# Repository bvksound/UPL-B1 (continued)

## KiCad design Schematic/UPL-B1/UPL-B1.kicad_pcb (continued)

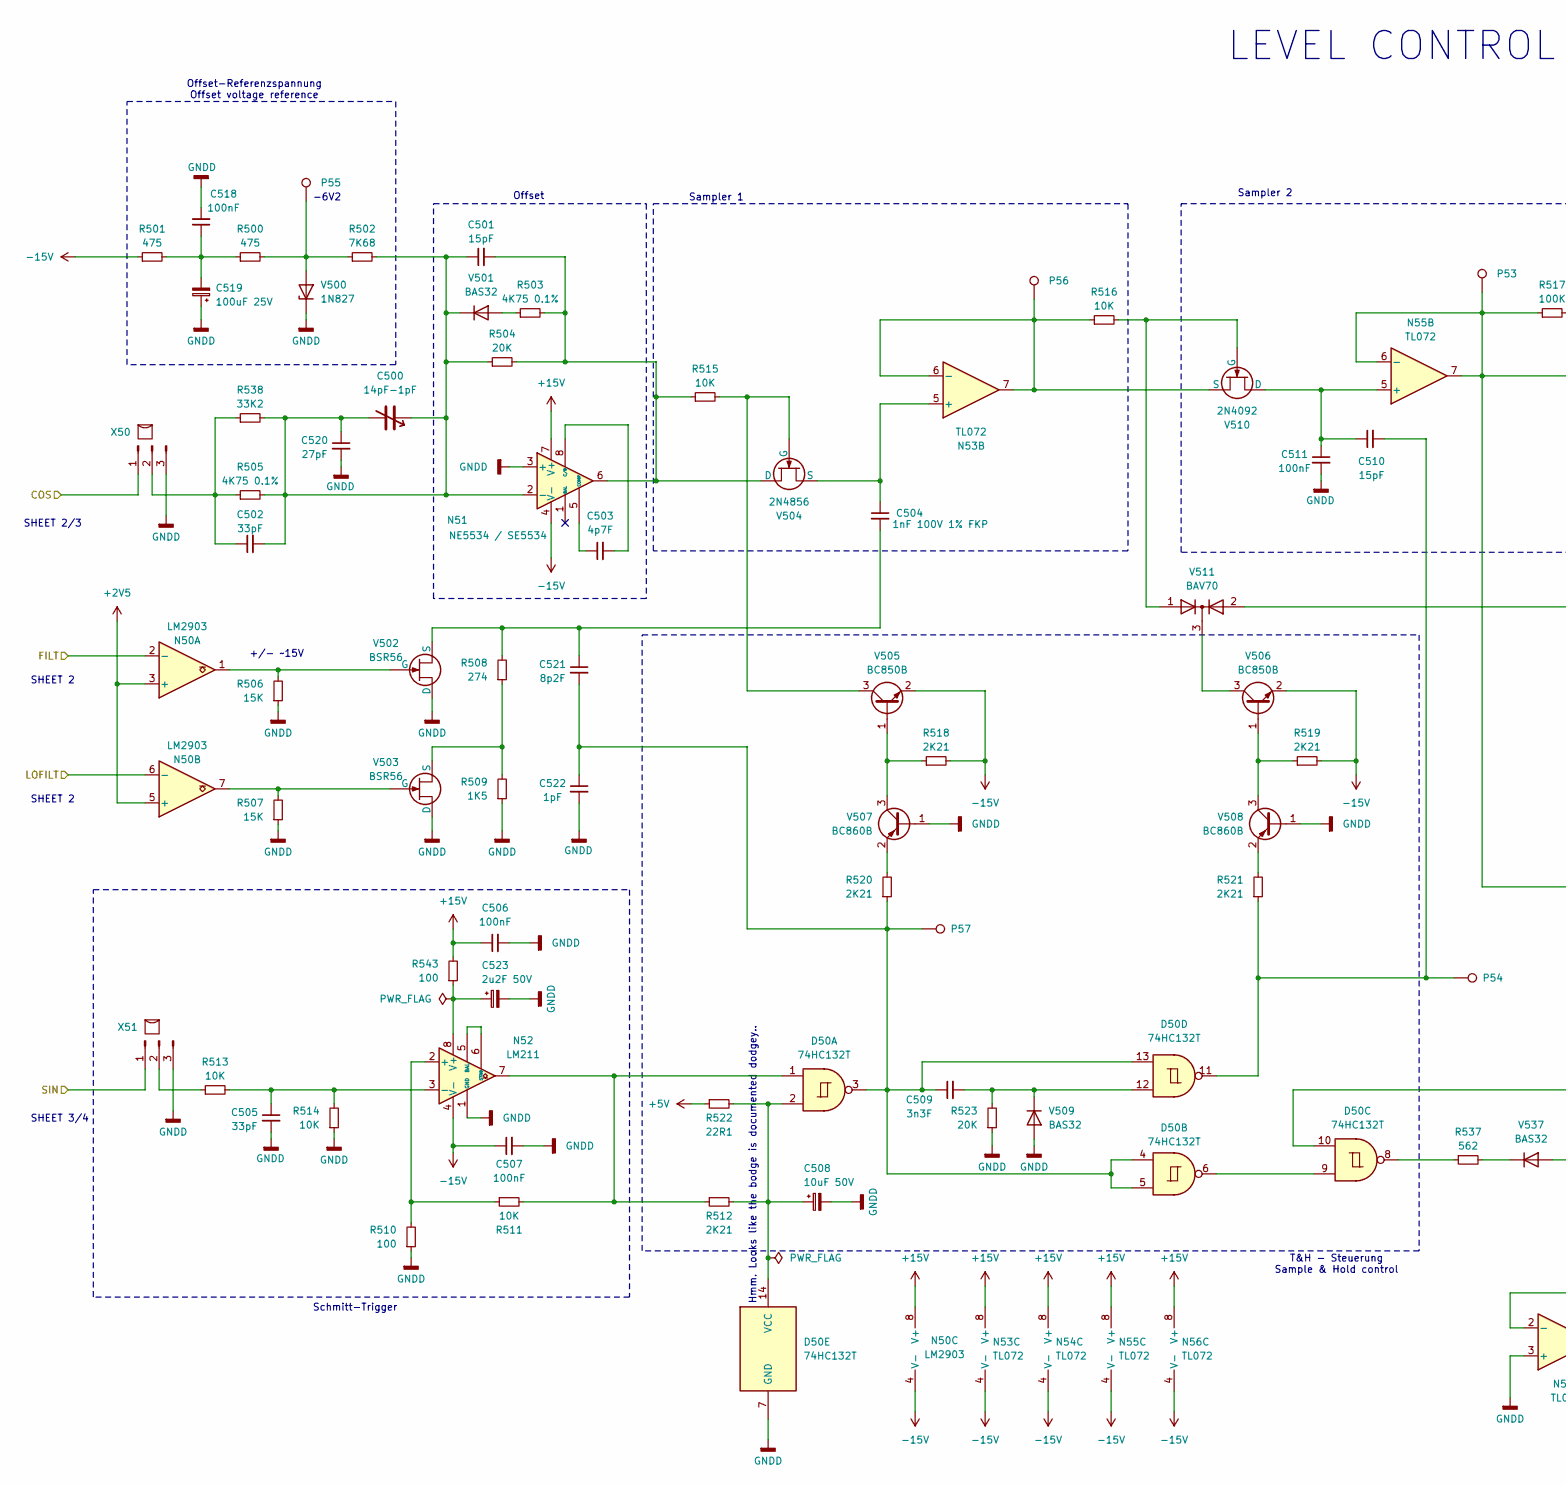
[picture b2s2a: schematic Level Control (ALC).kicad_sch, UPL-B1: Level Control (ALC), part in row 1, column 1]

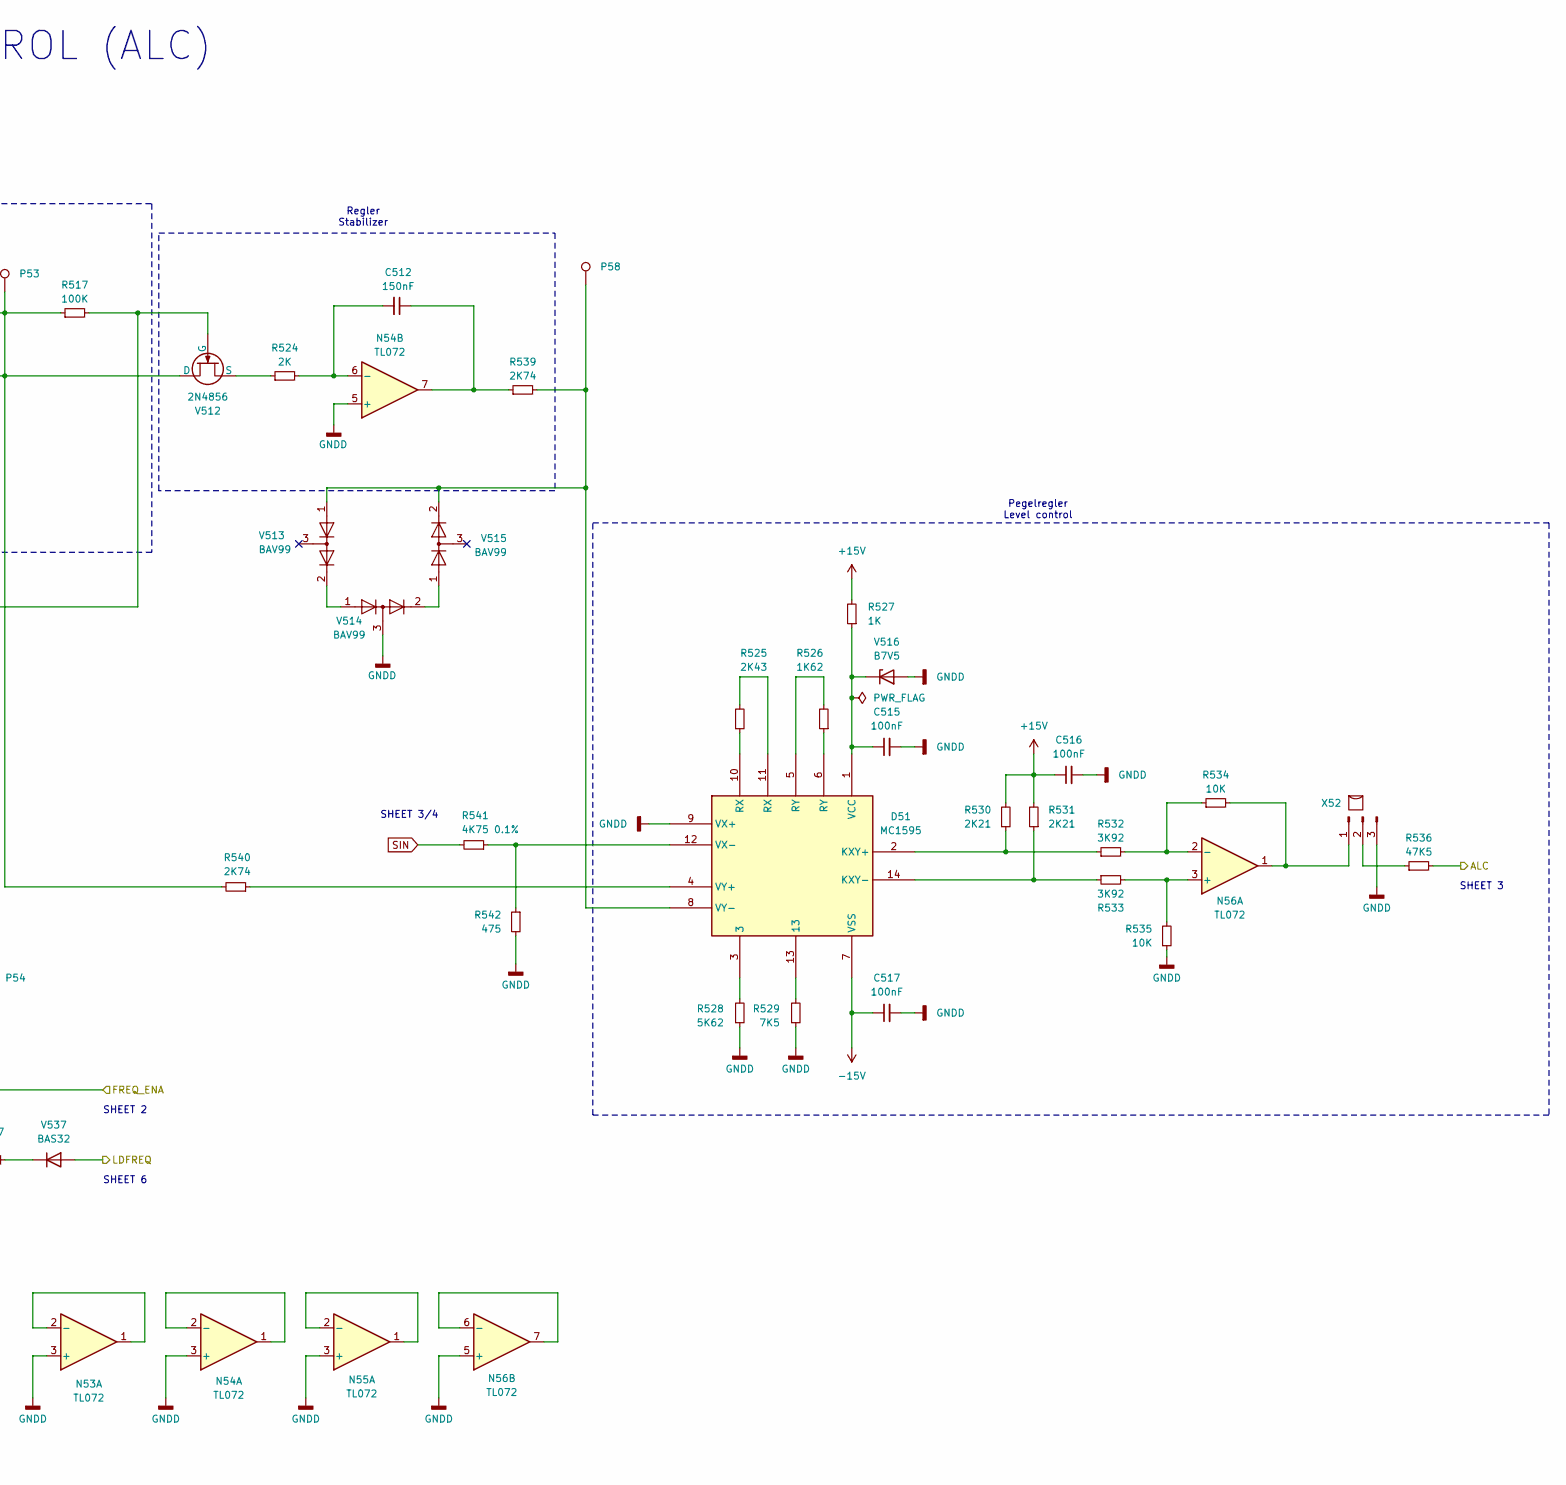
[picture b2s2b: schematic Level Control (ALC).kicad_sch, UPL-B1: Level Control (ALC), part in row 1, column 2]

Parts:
C500: 14pF-1pF
C501, C510: 15pF; C_1206_3216Metric_Pad1.33x1.80mm_HandSolder
C502, C505: 33pF; C_1206_3216Metric_Pad1.33x1.80mm_HandSolder
C503: 4p7F; C_1206_3216Metric_Pad1.33x1.80mm_HandSolder
C504: 1nF 100V 1% FKP
C506, C507, C511, C515, C516, C517, C518: 100nF; C_1206_3216Metric_Pad1.33x1.80mm_HandSolder
C508: 10uF 50V; C_Radial_D6.3mm_H11.0mm_P2.50mm
C509: 3n3F; C_1206_3216Metric_Pad1.33x1.80mm_HandSolder
C512: 150nF
C519: 100uF 25V; C_Radial_D6.3mm_H11.0mm_P2.50mm
C520: 27pF; C_1206_3216Metric_Pad1.33x1.80mm_HandSolder
C521: 8p2F; C_1206_3216Metric_Pad1.33x1.80mm_HandSolder
C522: 1pF; C_1206_3216Metric_Pad1.33x1.80mm_HandSolder
C523: 2u2F 50V; C_Radial_D6.3mm_H11.0mm_P2.50mm
D50: 74HC132T; SOIC-14_3.9x8.7mm_P1.27mm
D51: MC1595; DIP-14_W7.62mm
N50: LM2903; SOIC-8_3.9x4.9mm_P1.27mm
N51: NE5534 / SE5534; SOIC-8_3.9x4.9mm_P1.27mm
N52: LM211; SOIC-8_3.9x4.9mm_P1.27mm
N53, N54, N55, N56: TL072; SOIC-8_3.9x4.9mm_P1.27mm
P53, P54, P55, P56, P57, P58: TestPoint; PinHeader_1x01_P1.00mm_Vertical
R500, R501, R542: 475; R_1206_3216Metric_Pad1.30x1.75mm_HandSolder
R502: 7K68; R_Axial_DIN0204_L3.6mm_D1.6mm_P7.62mm_Horizontal
R503, R541: 4K75 0.1%; R_1206_3216Metric_Pad1.30x1.75mm_HandSolder
R504, R523: 20K; R_1206_3216Metric_Pad1.30x1.75mm_HandSolder
R505: 4K75 0.1%; R_Axial_DIN0204_L3.6mm_D1.6mm_P7.62mm_Horizontal
R506, R507: 15K; R_1206_3216Metric_Pad1.30x1.75mm_HandSolder
R508: 274; R_1206_3216Metric_Pad1.30x1.75mm_HandSolder
R509: 1K5; R_1206_3216Metric_Pad1.30x1.75mm_HandSolder
R510, R543: 100; R_1206_3216Metric_Pad1.30x1.75mm_HandSolder
R511, R513, R514, R515, R516, R534, R535: 10K; R_1206_3216Metric_Pad1.30x1.75mm_HandSolder
R512, R518, R519, R520, R521, R530, R531: 2K21; R_1206_3216Metric_Pad1.30x1.75mm_HandSolder
R517: 100K; R_1206_3216Metric_Pad1.30x1.75mm_HandSolder
R522: 22R1; R_1206_3216Metric_Pad1.30x1.75mm_HandSolder
R524: 2K; R_1206_3216Metric_Pad1.30x1.75mm_HandSolder
R525: 2K43; R_1206_3216Metric_Pad1.30x1.75mm_HandSolder
R526: 1K62; R_1206_3216Metric_Pad1.30x1.75mm_HandSolder
R527: 1K; R_1206_3216Metric_Pad1.30x1.75mm_HandSolder
R528: 5K62; R_1206_3216Metric_Pad1.30x1.75mm_HandSolder
R529: 7K5; R_1206_3216Metric_Pad1.30x1.75mm_HandSolder
R532, R533: 3K92; R_1206_3216Metric_Pad1.30x1.75mm_HandSolder
R536: 47K5; R_1206_3216Metric_Pad1.30x1.75mm_HandSolder
R537: 562; R_1206_3216Metric_Pad1.30x1.75mm_HandSolder
R538: 33K2; R_1206_3216Metric_Pad1.30x1.75mm_HandSolder
R539, R540: 2K74; R_1206_3216Metric_Pad1.30x1.75mm_HandSolder
V500: 1N827; D_DO-35_SOD27_P7.62mm_Horizontal
V501, V509, V537: BAS32; D_SOD-523
V502, V503: BSR56; SOT-23
V504, V512: 2N4856; TO-52-3
V505, V506: BC850B; SOT-23
V507, V508: BC860B; SOT-23
V510: 2N4092; TO-52-3
V511: BAV70; SOT-23
V513, V514, V515: BAV99; SOT-23
V516: B7V5; D_DO-41_SOD81_P10.16mm_Horizontal
X50, X51, X52: Conn_01x03_Pin_Bridge; PinHeader_1x03_P2.54mm_Vertical

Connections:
+2V5: N50.3 (+), N50.5 (+); also elsewhere on the board
+5V: R522.1; also elsewhere on the board
+15V: C506.1, C516.1, N50.8 (V+), N51.7 (V+), N53.8 (V+), N54.8 (V+), N55.8 (V+), N56.8 (V+), R527.2, R530.2, R531.2, R543.2; also elsewhere on the board
-15V: C507.1, C517.1, D51.7 (VSS), N50.4 (V-), N51.4 (V-), N52.4 (V-), N53.4 (V-), N54.4 (V-), N55.4 (V-), N56.4 (V-), R501.1, R518.2, R519.2, V505.2 (E), V506.2 (E); also elsewhere on the board
/COS: X50.1; also elsewhere on the board
/Integrator 1 & Loop Inverter/ALC: R536.2; also elsewhere on the board
/Level Control (ALC)/FILT: N50.2 (-); also elsewhere on the board
/Level Control (ALC)/FREQ_ENA: D50.10; also elsewhere on the board
/Level Control (ALC)/LDFREQ: V537.2 (A)
/Level Control (ALC)/LOFILT: N50.6 (-); also elsewhere on the board
GNDD: C505.2, C506.2, C507.2, C508.2, C511.2, C515.2, C516.2, C517.2, C518.2, C519.1, C520.2, C522.2, C523.2, D50.7 (GND), D51.9 (VX+), N51.3 (+), N52.1 (GND), N53.3 (+), N54.3 (+), N54.5 (+), N55.3 (+), N56.5 (+), R506.1, R507.1, R509.1, R510.1, R514.1, R523.1, R528.1, R529.1, R535.1, R542.2, V500.1 (K), V502.1 (D), V503.1 (D), V507.1 (B), V508.1 (B), V509.2 (A), V514.3 (K), V516.2 (A), X50.3, X51.3, X52.3; also elsewhere on the board
unnamed: C509.1, C521.2, C522.1, D50.3, D50.4, D50.5, D50.13, P57.1, R520.1
unnamed: C510.2, D50.11, P54.1, R521.1
unnamed: C512.1, N54.7, R539.1
unnamed: C518.1, C519.2, R500.1, R501.2
unnamed: D50.1, N52.7, R511.2, R512.1
unnamed: D50.6, D50.9
unnamed: D50.8, R537.1
unnamed: C508.1, D50.2, D50.14 (VCC), R512.2, R522.2
unnamed: D51.2 (KXY+), R530.1, R532.1
unnamed: D51.14 (KXY-), R531.1, R533.1
unnamed: D51.3, R528.2
unnamed: D51.13, R529.2
unnamed: D51.10 (RX), R525.1
unnamed: D51.11 (RX), R525.2
unnamed: D51.5 (RY), R526.2
unnamed: D51.6 (RY), R526.1
unnamed: C515.1, D51.1 (VCC), R527.1, V516.1 (K)
unnamed: D51.12 (VX-), R541.1, R542.1
unnamed: D51.4 (VY+), R540.1
unnamed: D51.8 (VY-), P58.1, R539.2, V513.1 (K), V515.2 (A)
unnamed: C500.1, C500.2, C501.1, C502.2, C520.1, N51.2 (-), R502.2, R504.1, R505.2, R538.2, V501.1 (K)
unnamed: C503.1, N51.5 (COMP)
unnamed: C503.2, N51.8 (C/B)
unnamed: N52.2 (+), R510.2, R511.1
unnamed: C505.1, N52.3 (-), R513.2, R514.2
unnamed: N52.5 (BAL), N52.6 (STRB)
unnamed: C523.1, N52.8 (V+), R543.1
unnamed: N53.1, N53.2 (-)
unnamed: C504.1, N53.5 (+), V504.3 (S)
unnamed: N53.6 (-), N53.7, P56.1, R516.1, V510.3 (S)
unnamed: N54.1, N54.2 (-)
unnamed: C512.2, N54.6 (-), R524.2
unnamed: N55.1, N55.2 (-)
unnamed: C510.1, C511.1, N55.5 (+), V510.1 (D)
unnamed: N55.6 (-), N55.7, P53.1, R517.1, R540.2, V512.1 (D)
unnamed: N56.3 (+), R533.2, R535.2
unnamed: N56.2 (-), R532.2, R534.1
unnamed: N56.6 (-), N56.7
unnamed: P55.1, R500.2, R502.1, V500.2 (A)
unnamed: R503.1, V501.2 (A)
unnamed: N50.1, R506.2, V502.2 (G)
unnamed: C504.2, C521.1, R508.2, V502.3 (S)
unnamed: N50.7, R507.2, V503.2 (G)
unnamed: R508.1, R509.2, V503.3 (S)
unnamed: C501.2, N51.6, R503.2, R504.2, R515.1, V504.1 (D)
unnamed: R515.2, V504.2 (G), V505.3 (C)
unnamed: R518.1, V505.1 (B), V507.3 (C)
unnamed: R519.1, V506.1 (B), V508.3 (C)
unnamed: V506.3 (C), V511.3 (K)
unnamed: R520.2, V507.2 (E)
unnamed: R521.2, V508.2 (E)
unnamed: C509.2, D50.12, R523.2, V509.1 (K)
unnamed: R516.2, V510.2 (G), V511.1 (A)
unnamed: R517.2, V511.2 (A), V512.2 (G)
unnamed: R524.1, V512.3 (S)
unnamed: V513.2 (A), V514.1 (K)
unnamed: V514.2 (A), V515.1 (K)
unnamed: R537.2, V537.1 (K)
unnamed: C502.1, R505.1, R538.1, X50.2
unnamed: R513.1, X51.2
unnamed: N56.1, R534.2, X52.1
unnamed: R536.1, X52.2
SIN: R541.2, X51.1; also elsewhere on the board

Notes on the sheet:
Regler Stabilizer
Schmitt-Trigger
SHEET 2
+/- ~15V
LEVEL CONTROL (ALC)
SHEET 2/3
SHEET 3/4
SHEET 6
Sampler 1
Sampler 2
-6V2
Offset
Hmm. Looks like the bodge is documented dodgey..
SHEET 3
Pegelregler Level control
Offset-Referenzspannung Offset voltage reference
T&H - Steuerung Sample & Hold control

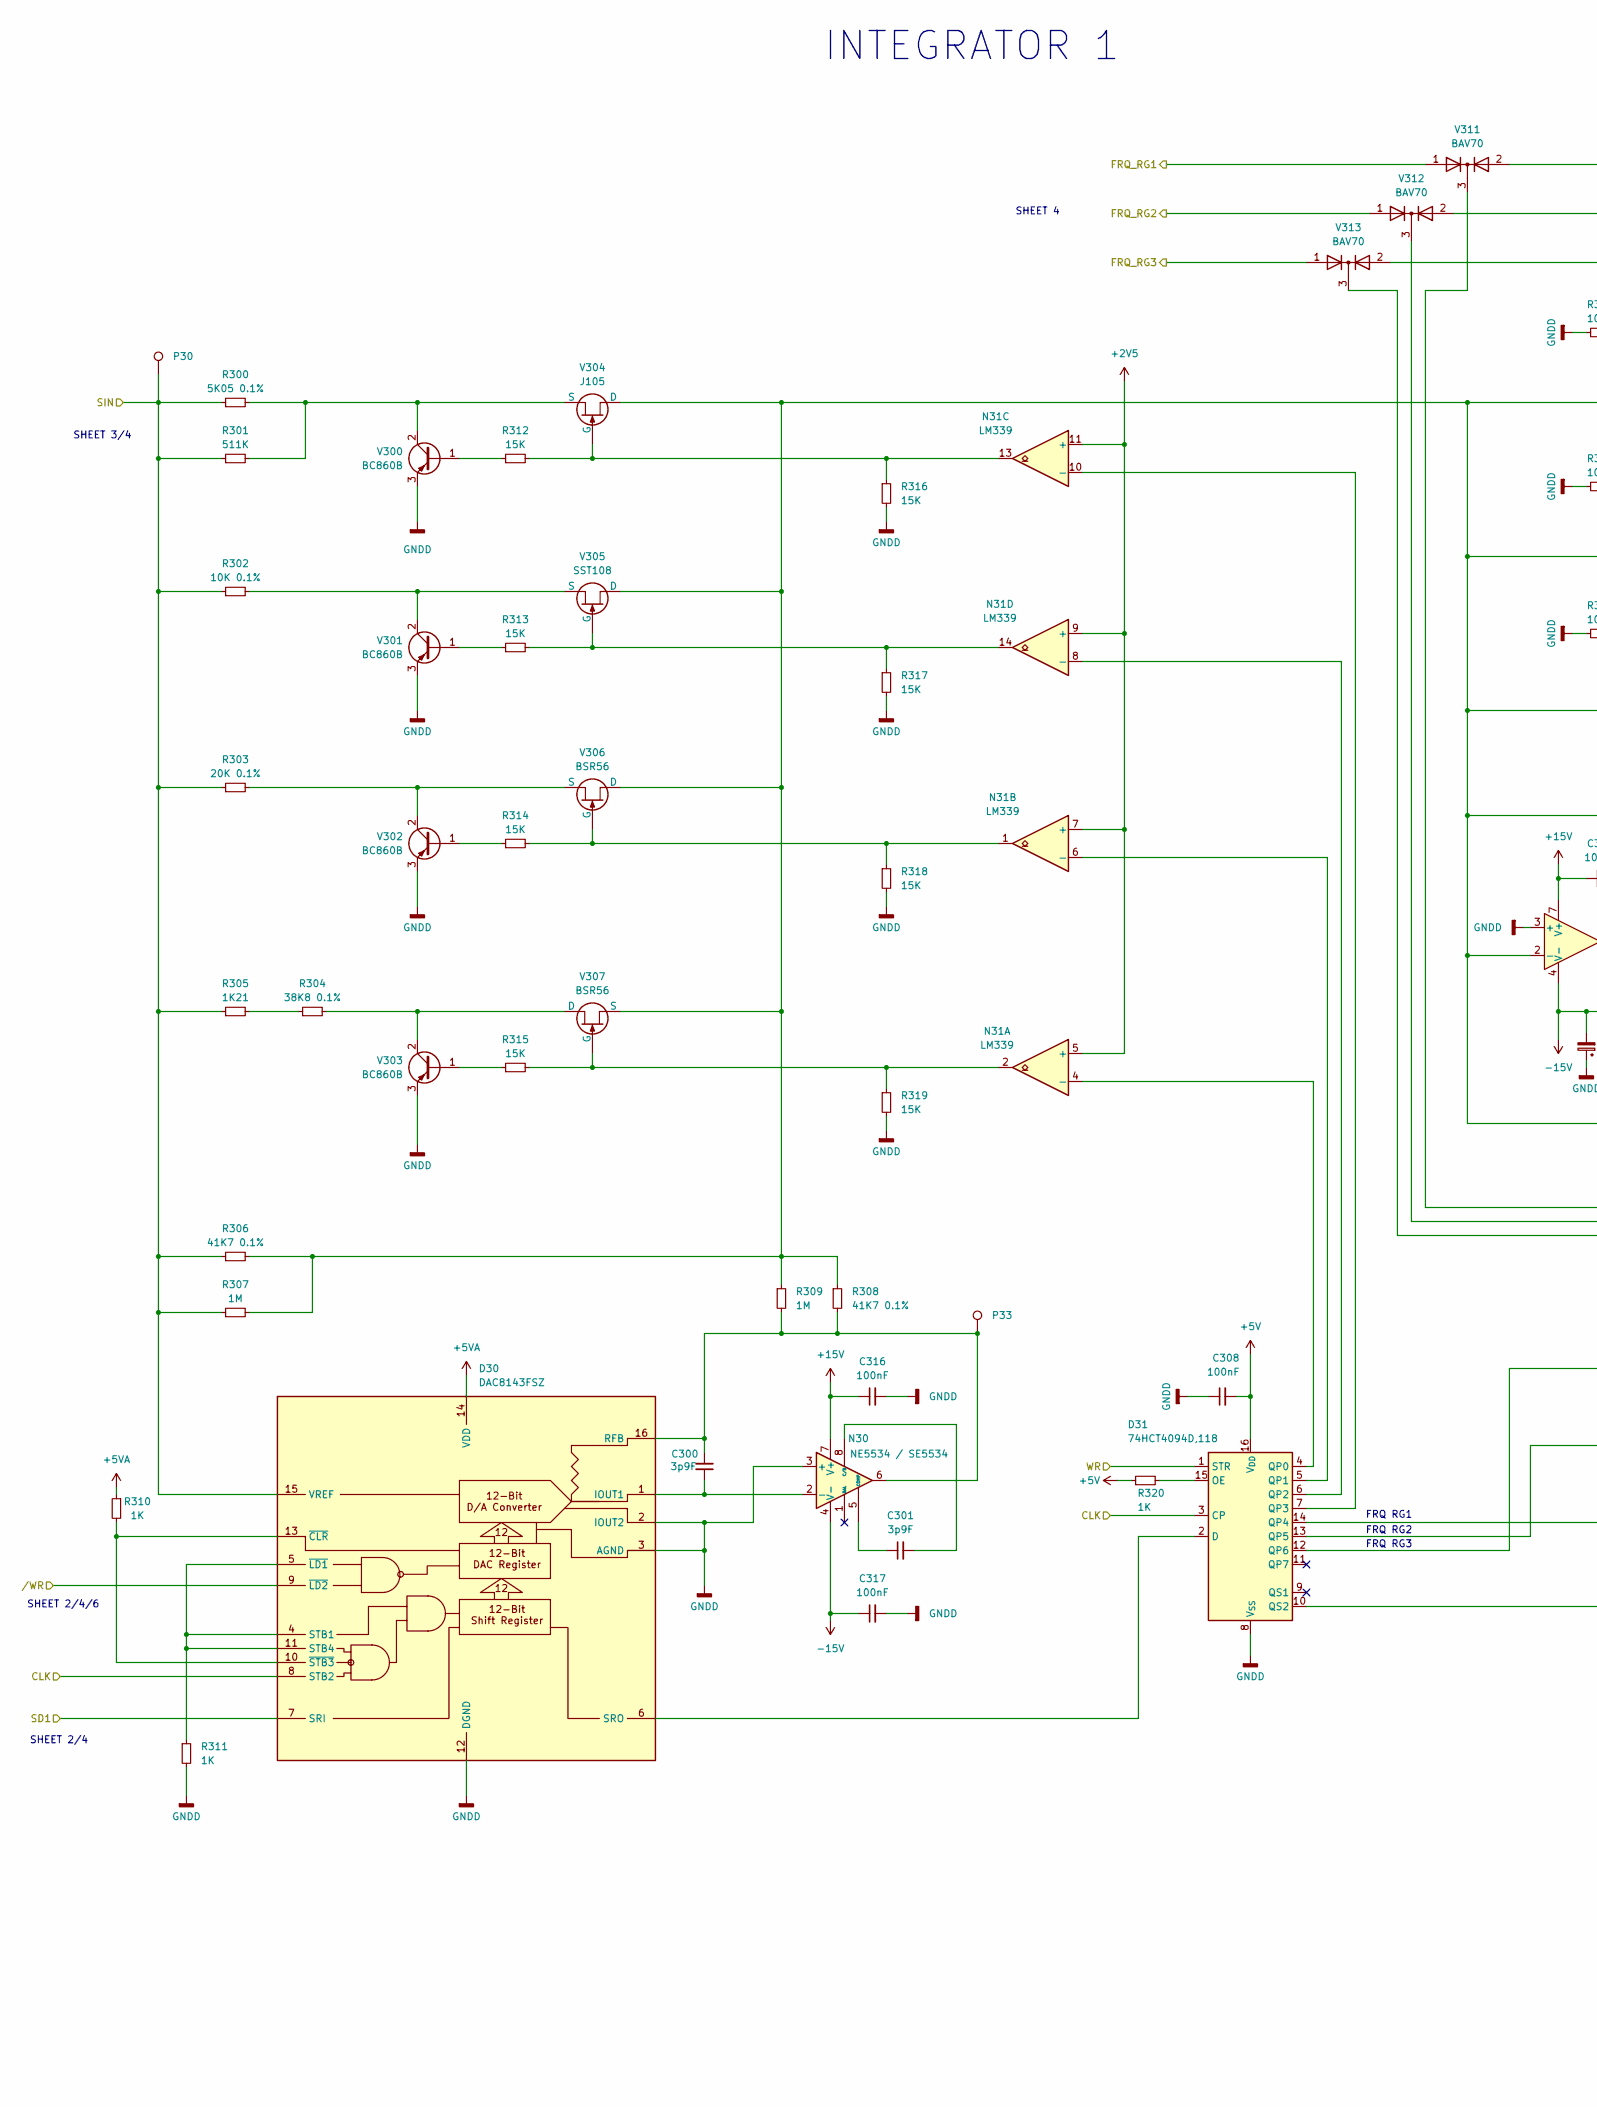
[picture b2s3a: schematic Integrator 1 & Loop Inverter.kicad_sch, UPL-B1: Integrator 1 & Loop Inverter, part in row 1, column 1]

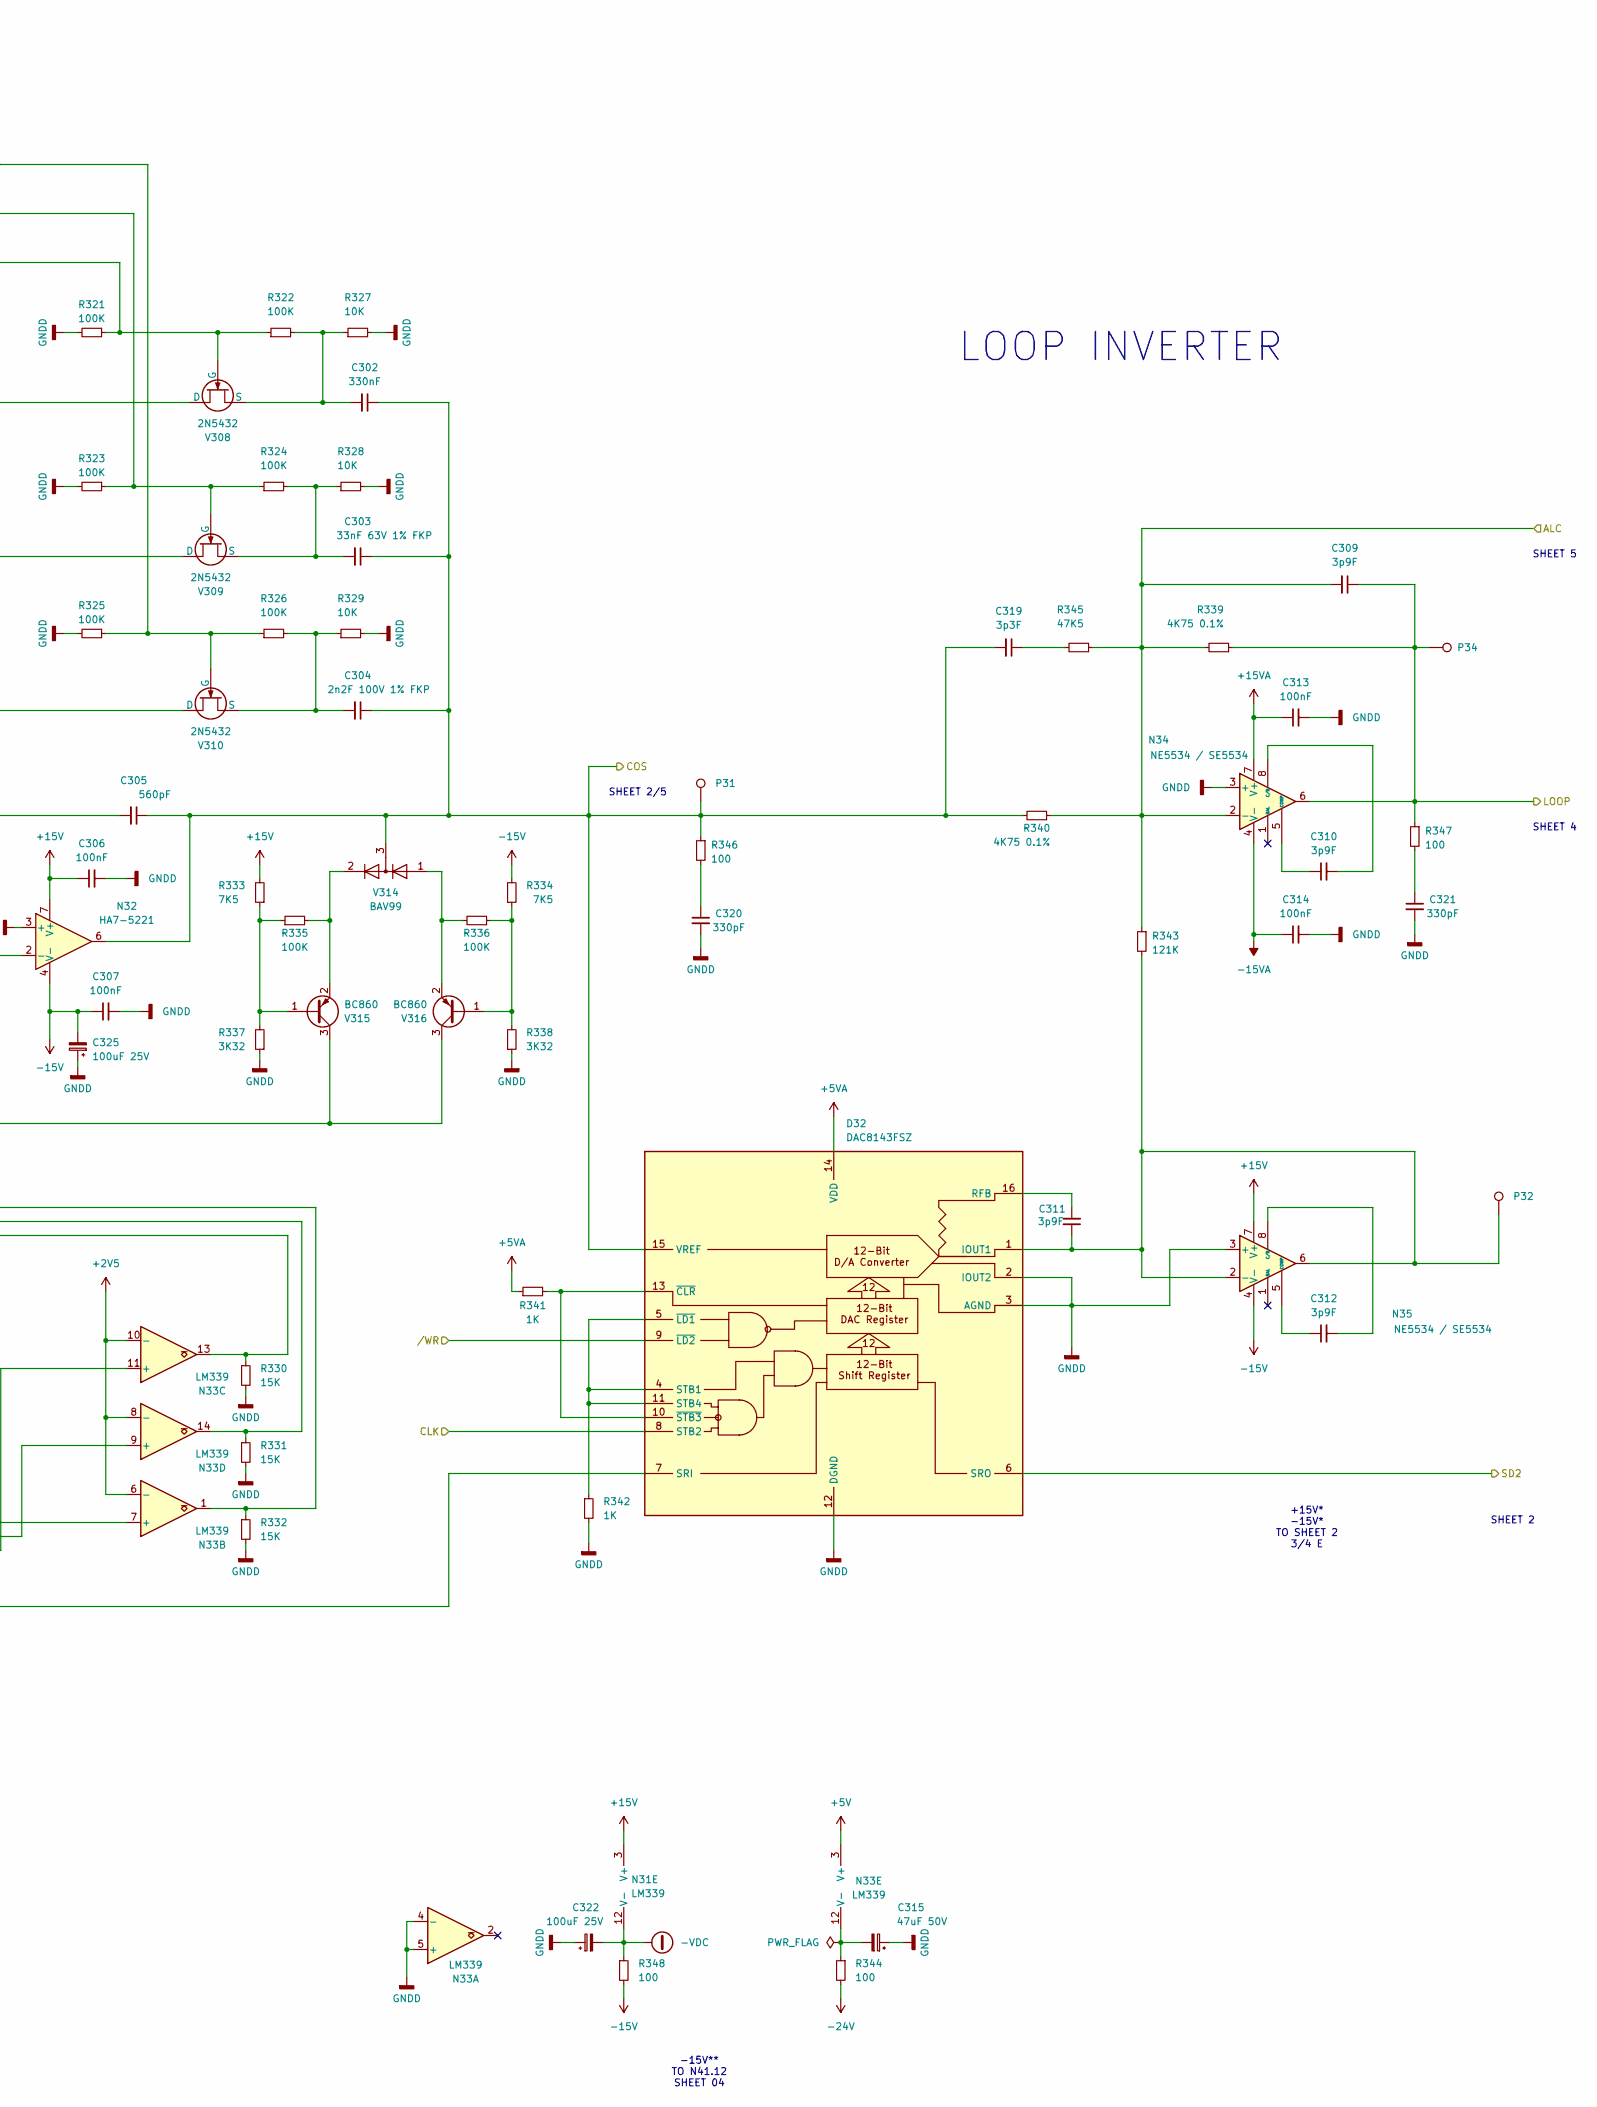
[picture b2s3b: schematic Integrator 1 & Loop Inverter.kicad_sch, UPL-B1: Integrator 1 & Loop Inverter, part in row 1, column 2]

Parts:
C300, C301, C309, C310, C311, C312: 3p9F; C_1206_3216Metric_Pad1.33x1.80mm_HandSolder
C302: 330nF; C_Axial_L17.0mm_D7.0mm_P25.00mm_Horizontal
C303: 33nF 63V 1% FKP
C304: 2n2F 100V 1% FKP
C305: 560pF; C_1206_3216Metric_Pad1.33x1.80mm_HandSolder
C306, C307, C308, C313, C314, C316, C317: 100nF; C_1206_3216Metric_Pad1.33x1.80mm_HandSolder
C315: 47uF 50V; C_Radial_D6.3mm_H11.0mm_P2.50mm
C319: 3p3F; C_1206_3216Metric_Pad1.33x1.80mm_HandSolder
C320, C321: 330pF; C_1206_3216Metric_Pad1.33x1.80mm_HandSolder
C322, C325: 100uF 25V; C_Radial_D6.3mm_H11.0mm_P2.50mm
D30, D32: DAC8143FSZ; SOIC-16W_7.5x10.3mm_P1.27mm; Manufacturer_Part_Number DAC8143FSZ
D31: 74HCT4094D,118; SOIC-16_3.9x9.9mm_P1.27mm; Mouser Part Number 771-74HCT4094D-T
N30, N34, N35: NE5534 / SE5534; SOIC-8_3.9x4.9mm_P1.27mm
N31, N33: LM339; SOIC-14_3.9x8.7mm_P1.27mm
N32: HA7-5221; MSOP-8_3x3mm_P0.65mm
P30, P31, P32, P33, P34: TestPoint; PinHeader_1x01_P1.00mm_Vertical
R300: 5K05 0.1%; R_Axial_DIN0204_L3.6mm_D1.6mm_P7.62mm_Horizontal
R301: 511K; R_1206_3216Metric_Pad1.30x1.75mm_HandSolder
R302: 10K 0.1%; R_Axial_DIN0204_L3.6mm_D1.6mm_P7.62mm_Horizontal
R303: 20K 0.1%; R_Axial_DIN0204_L3.6mm_D1.6mm_P7.62mm_Horizontal
R304: 38K8 0.1%; R_Axial_DIN0204_L3.6mm_D1.6mm_P7.62mm_Horizontal
R305: 1K21; R_1206_3216Metric_Pad1.30x1.75mm_HandSolder
R306, R308: 41K7 0.1%; R_Axial_DIN0204_L3.6mm_D1.6mm_P7.62mm_Horizontal
R307, R309: 1M; R_1206_3216Metric_Pad1.30x1.75mm_HandSolder
R310, R311, R320, R341, R342: 1K; R_1206_3216Metric_Pad1.30x1.75mm_HandSolder
R312, R313, R314, R315, R316, R317, R318, R319, R330, R331, R332: 15K; R_1206_3216Metric_Pad1.30x1.75mm_HandSolder
R321, R322, R323, R324, R325, R326, R335, R336: 100K; R_1206_3216Metric_Pad1.30x1.75mm_HandSolder
R327, R328, R329: 10K; R_1206_3216Metric_Pad1.30x1.75mm_HandSolder
R333, R334: 7K5; R_1206_3216Metric_Pad1.30x1.75mm_HandSolder
R337, R338: 3K32; R_1206_3216Metric_Pad1.30x1.75mm_HandSolder
R339, R340: 4K75 0.1%; R_Axial_DIN0204_L3.6mm_D1.6mm_P7.62mm_Horizontal
R343: 121K; R_1206_3216Metric_Pad1.30x1.75mm_HandSolder
R344, R346, R347, R348: 100; R_1206_3216Metric_Pad1.30x1.75mm_HandSolder
R345: 47K5; R_1206_3216Metric_Pad1.30x1.75mm_HandSolder
V300, V301, V302, V303: BC860B; SOT-23
V304: J105; TO-92L_Inline
V305: SST108; SOT-23
V306, V307: BSR56; SOT-23
V308, V309, V310: 2N5432; TO-52-3
V311, V312, V313: BAV70; SOT-23
V314: BAV99; SOT-23
V315, V316: BC860; SOT-23

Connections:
+2V5: N31.5 (+), N31.7 (+), N31.9 (+), N31.11 (+), N33.6 (-), N33.8 (-), N33.10 (-); also elsewhere on the board
+5V: C308.2, D31.16 (V_{DD}), N33.3 (V+), R320.1; also elsewhere on the board
+5VA: D30.14 (VDD), D32.14 (VDD), R310.1, R341.1; also elsewhere on the board
+15V: C306.1, C316.1, N30.7 (V+), N31.3 (V+), N32.7 (V+), N35.7 (V+), R333.2; also elsewhere on the board
+15VA: C313.1, N34.7 (V+); also elsewhere on the board
-15V: C307.1, C317.1, C325.2, N30.4 (V-), N32.4 (V-), N35.4 (V-), R334.2, R348.2; also elsewhere on the board
-15VA: C314.1, N34.4 (V-); also elsewhere on the board
-24V: R344.2; also elsewhere on the board
-VDC: C322.2, N31.12 (V-), R348.1; also elsewhere on the board
/CLK: D30.8 (STB2), D31.3 (CP), D32.8 (STB2); also elsewhere on the board
/COS: C302.1, C303.1, C304.1, C305.1, C319.2, D32.15 (VREF), N32.6, P31.1, R340.2, R346.1, V314.3 (K); also elsewhere on the board
/Integrator 1 & Loop Inverter/ALC: C309.2, N34.2 (-), R339.2, R340.1, R343.1, R345.1; also elsewhere on the board
/Integrator 1 & Loop Inverter/FRQ_RG1: V311.1 (A); also elsewhere on the board
/Integrator 1 & Loop Inverter/FRQ_RG2: V312.1 (A); also elsewhere on the board
/Integrator 1 & Loop Inverter/FRQ_RG3: V313.1 (A); also elsewhere on the board
/Integrator 1 & Loop Inverter/SD2: D32.6 (SRO); also elsewhere on the board
/Integrator 1 & Loop Inverter/WR: D31.1 (STR)
/LOOP: C309.1, N34.6, P34.1, R339.1, R347.1; also elsewhere on the board
/SD1: D30.7 (SRI); also elsewhere on the board
/~WR: D30.9 (~LD2), D32.9 (~LD2); also elsewhere on the board
GNDD: C306.2, C307.2, C308.1, C313.2, C314.2, C315.1, C316.2, C317.2, C320.2, C321.2, C322.1, C325.1, D30.2 (IOUT2), D30.3 (AGND), D30.12 (DGND), D31.8 (V_{SS}), D32.2 (IOUT2), D32.3 (AGND), D32.12 (DGND), N30.3 (+), N32.3 (+), N33.4 (-), N33.5 (+), N34.3 (+), N35.3 (+), R311.2, R316.2, R317.2, R318.2, R319.2, R321.2, R323.2, R325.2, R327.2, R328.2, R329.2, R330.2, R331.2, R332.2, R337.1, R338.1, R342.2, V300.3 (E), V301.3 (E), V302.3 (E), V303.3 (E); also elsewhere on the board
unnamed: C319.1, R345.2
unnamed: C320.1, R346.2
unnamed: C321.1, R347.2
unnamed: C300.1, D30.1 (IOUT1), N30.2 (-)
unnamed: C300.2, D30.16 (RFB), N30.6, P33.1, R308.2, R309.2
unnamed: D30.6 (SRO), D31.2 (D)
unnamed: D30.4 (STB1), D30.5 (~LD1), D30.11 (STB4), R311.1
unnamed: D30.10 (~STB3), D30.13 (~CLR), R310.2
unnamed: D31.15 (OE), R320.2
unnamed: D31.4 (QP0), N31.4 (-)
unnamed: D31.5 (QP1), N31.6 (-)
unnamed: D31.6 (QP2), N31.8 (-)
unnamed: D31.7 (QP3), N31.10 (-)
unnamed: D31.14 (QP4), N33.7 (+)
unnamed: D31.13 (QP5), N33.9 (+)
unnamed: D31.12 (QP6), N33.11 (+)
unnamed: D31.10 (QS2), D32.7 (SRI)
unnamed: C311.1, D32.1 (IOUT1), N35.2 (-), N35.6, P32.1, R343.2
unnamed: C311.2, D32.16 (RFB)
unnamed: D32.4 (STB1), D32.5 (~LD1), D32.11 (STB4), R342.1
unnamed: D32.10 (~STB3), D32.13 (~CLR), R341.2
unnamed: C301.1, N30.5 (COMP)
unnamed: C301.2, N30.8 (C/B)
unnamed: C305.2, N32.2 (-), R306.2, R307.2, R308.1, R309.1, V304.1 (D), V305.1 (D), V306.1 (D), V307.3 (S), V308.1 (D), V309.1 (D), V310.1 (D), V315.3 (C), V316.3 (C)
unnamed: C315.2, N33.12 (V-), R344.1
unnamed: C310.1, N34.5 (COMP)
unnamed: C310.2, N34.8 (C/B)
unnamed: C312.1, N35.5 (COMP)
unnamed: C312.2, N35.8 (C/B)
unnamed: R304.1, R305.2
unnamed: R312.1, V300.1 (B)
unnamed: R300.2, R301.2, V300.2 (C), V304.3 (S)
unnamed: R313.1, V301.1 (B)
unnamed: R302.2, V301.2 (C), V305.3 (S)
unnamed: R314.1, V302.1 (B)
unnamed: R303.2, V302.2 (C), V306.3 (S)
unnamed: R315.1, V303.1 (B)
unnamed: R304.2, V303.2 (C), V307.1 (D)
unnamed: N31.13, R312.2, R316.1, V304.2 (G)
unnamed: N31.14, R313.2, R317.1, V305.2 (G)
unnamed: N31.1, R314.2, R318.1, V306.2 (G)
unnamed: N31.2, R315.2, R319.1, V307.2 (G)
unnamed: R321.1, R322.1, V308.2 (G), V313.2 (A)
unnamed: C302.2, R322.2, R327.1, V308.3 (S)
unnamed: R323.1, R324.1, V309.2 (G), V312.2 (A)
unnamed: C303.2, R324.2, R328.1, V309.3 (S)
unnamed: R325.1, R326.1, V310.2 (G), V311.2 (A)
unnamed: C304.2, R326.2, R329.1, V310.3 (S)
unnamed: N33.1, R332.1, V311.3 (K)
unnamed: N33.14, R331.1, V312.3 (K)
unnamed: N33.13, R330.1, V313.3 (K)
unnamed: R335.2, V314.2 (A), V315.2 (E)
unnamed: R333.1, R335.1, R337.2, V315.1 (B)
unnamed: R334.1, R336.1, R338.2, V316.1 (B)
unnamed: R336.2, V314.1 (K), V316.2 (E)
SIN: D30.15 (VREF), P30.1, R300.1, R301.1, R302.1, R303.1, R305.1, R306.1, R307.1; also elsewhere on the board

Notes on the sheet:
INTEGRATOR 1
+15V* -15V* TO SHEET 2 3/4 E
SHEET 4
SHEET 2/4/6
FRQ RG1
LOOP INVERTER
FRQ RG3
SHEET 2/4
FRQ RG2
SHEET 3/4
SHEET 2/5
-15V** TO N41.12 SHEET 04
SHEET 2
SHEET 5
